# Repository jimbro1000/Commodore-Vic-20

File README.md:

# Commodore VIC-20 Schematic and PCB for assembly 250403

This repository contains KiCad schematics and "rough" PCB layout for the
cost reduced VIC-20, assembly #250403.

Originally hard forked from <https://github.com/StormTrooper/Commodore-Vic-20>
(this does not appear to be maintained).

The schematic for the Commodore VIC-20 (251027-01 Rev D) was taken from the
schematics on zimmers.net with extra detail from the "Vic-20 friendly computer
technical manual" and converted into KiCad (Version 8).

Additionally includes some KiCad footprints and symbols for the custom components.

## State

The schematics are complete and 95% of the PCB layout is done but it is not
complete. The power supply section of the board is mostly unfinished, and
accurate footprints for the large inductor, power switch and bridge rectifier are
needed.

## Notes

This is a WIP as the documentation and detail on the actual PCB are far from
clear and require some deciphering.

The power management section of the board in particular is unfinished.

The PCB design, while true to the original, is not intended for fabrication.
Instead the board has been reconstructed for the purpose of diagnosing faults
on original Commodore boards. The overall board dimensions are accurate but
the positioning of the different ports are approximations based on the rather
distorted board scans in the technical manual.

## KiCad thumbnail of schematic and pcb

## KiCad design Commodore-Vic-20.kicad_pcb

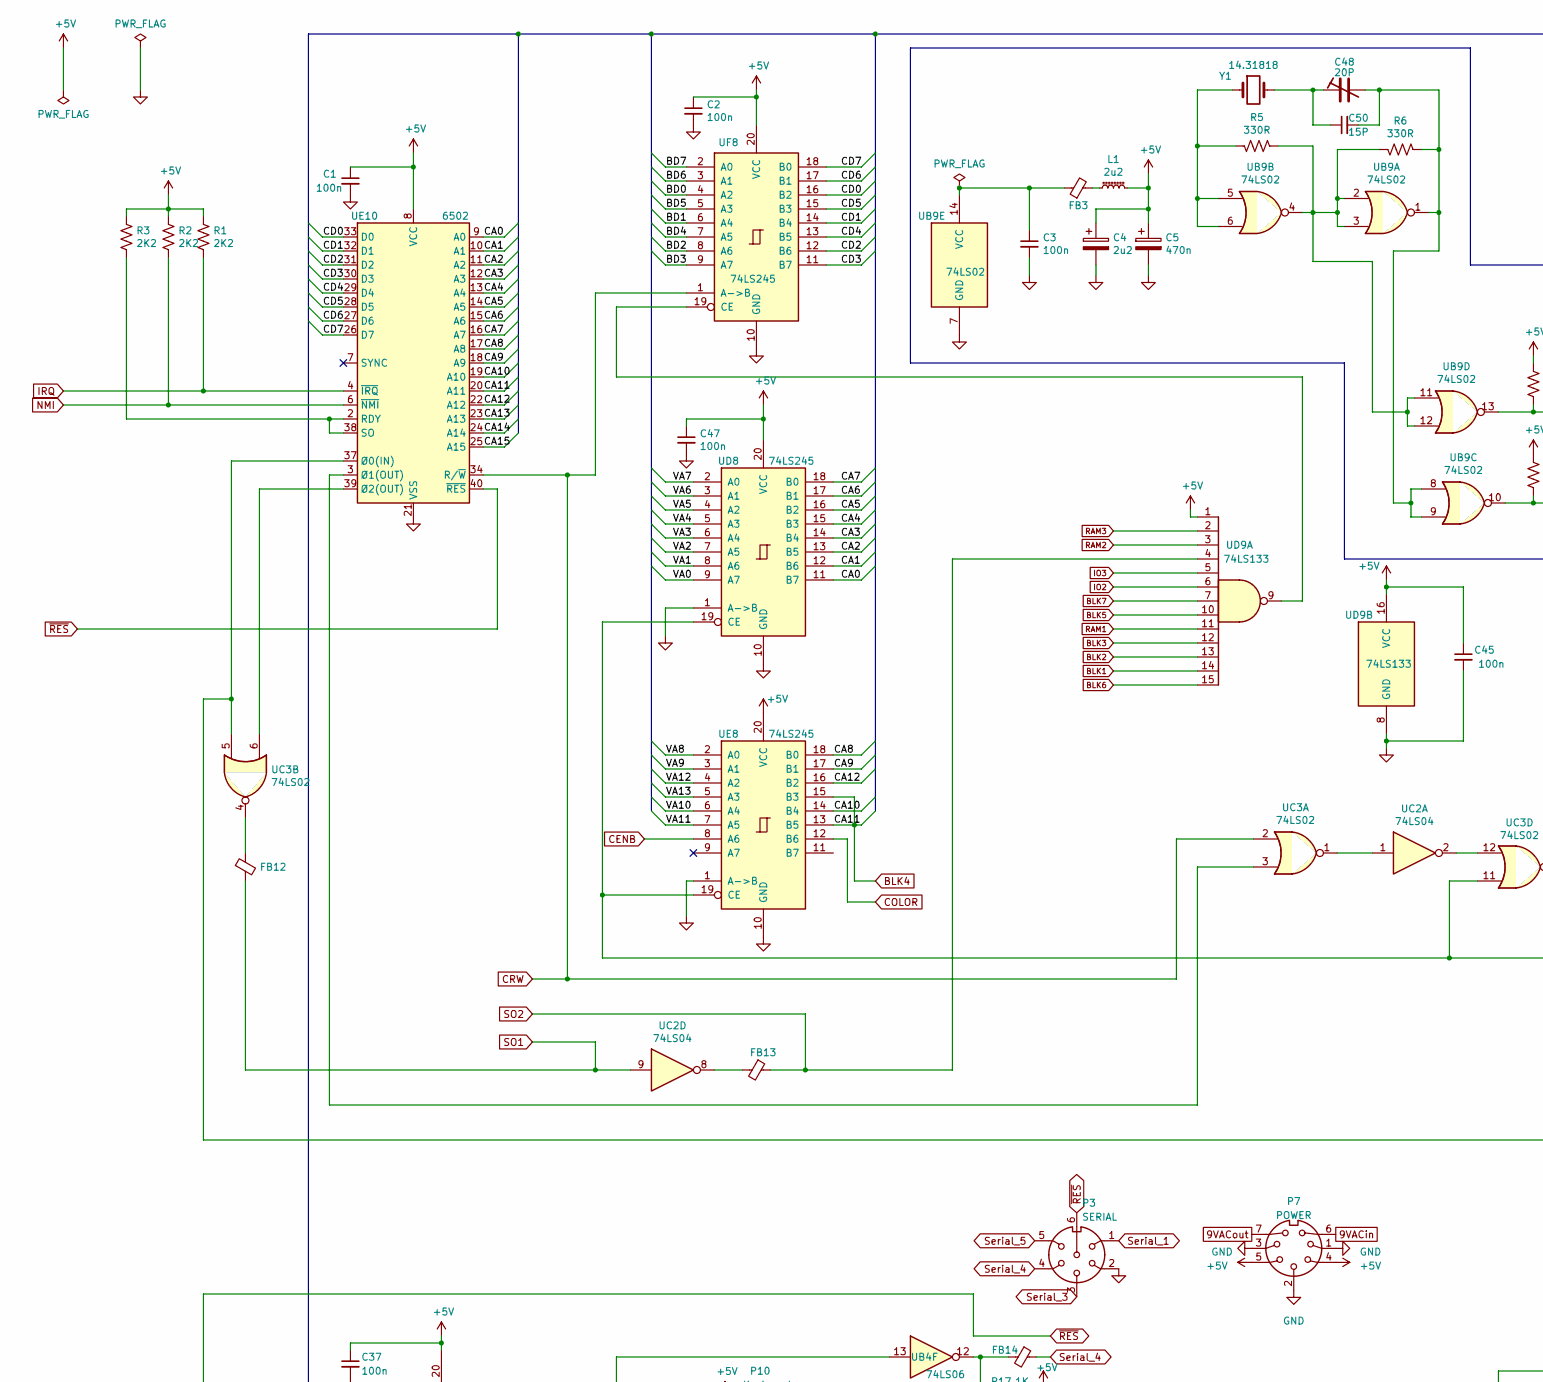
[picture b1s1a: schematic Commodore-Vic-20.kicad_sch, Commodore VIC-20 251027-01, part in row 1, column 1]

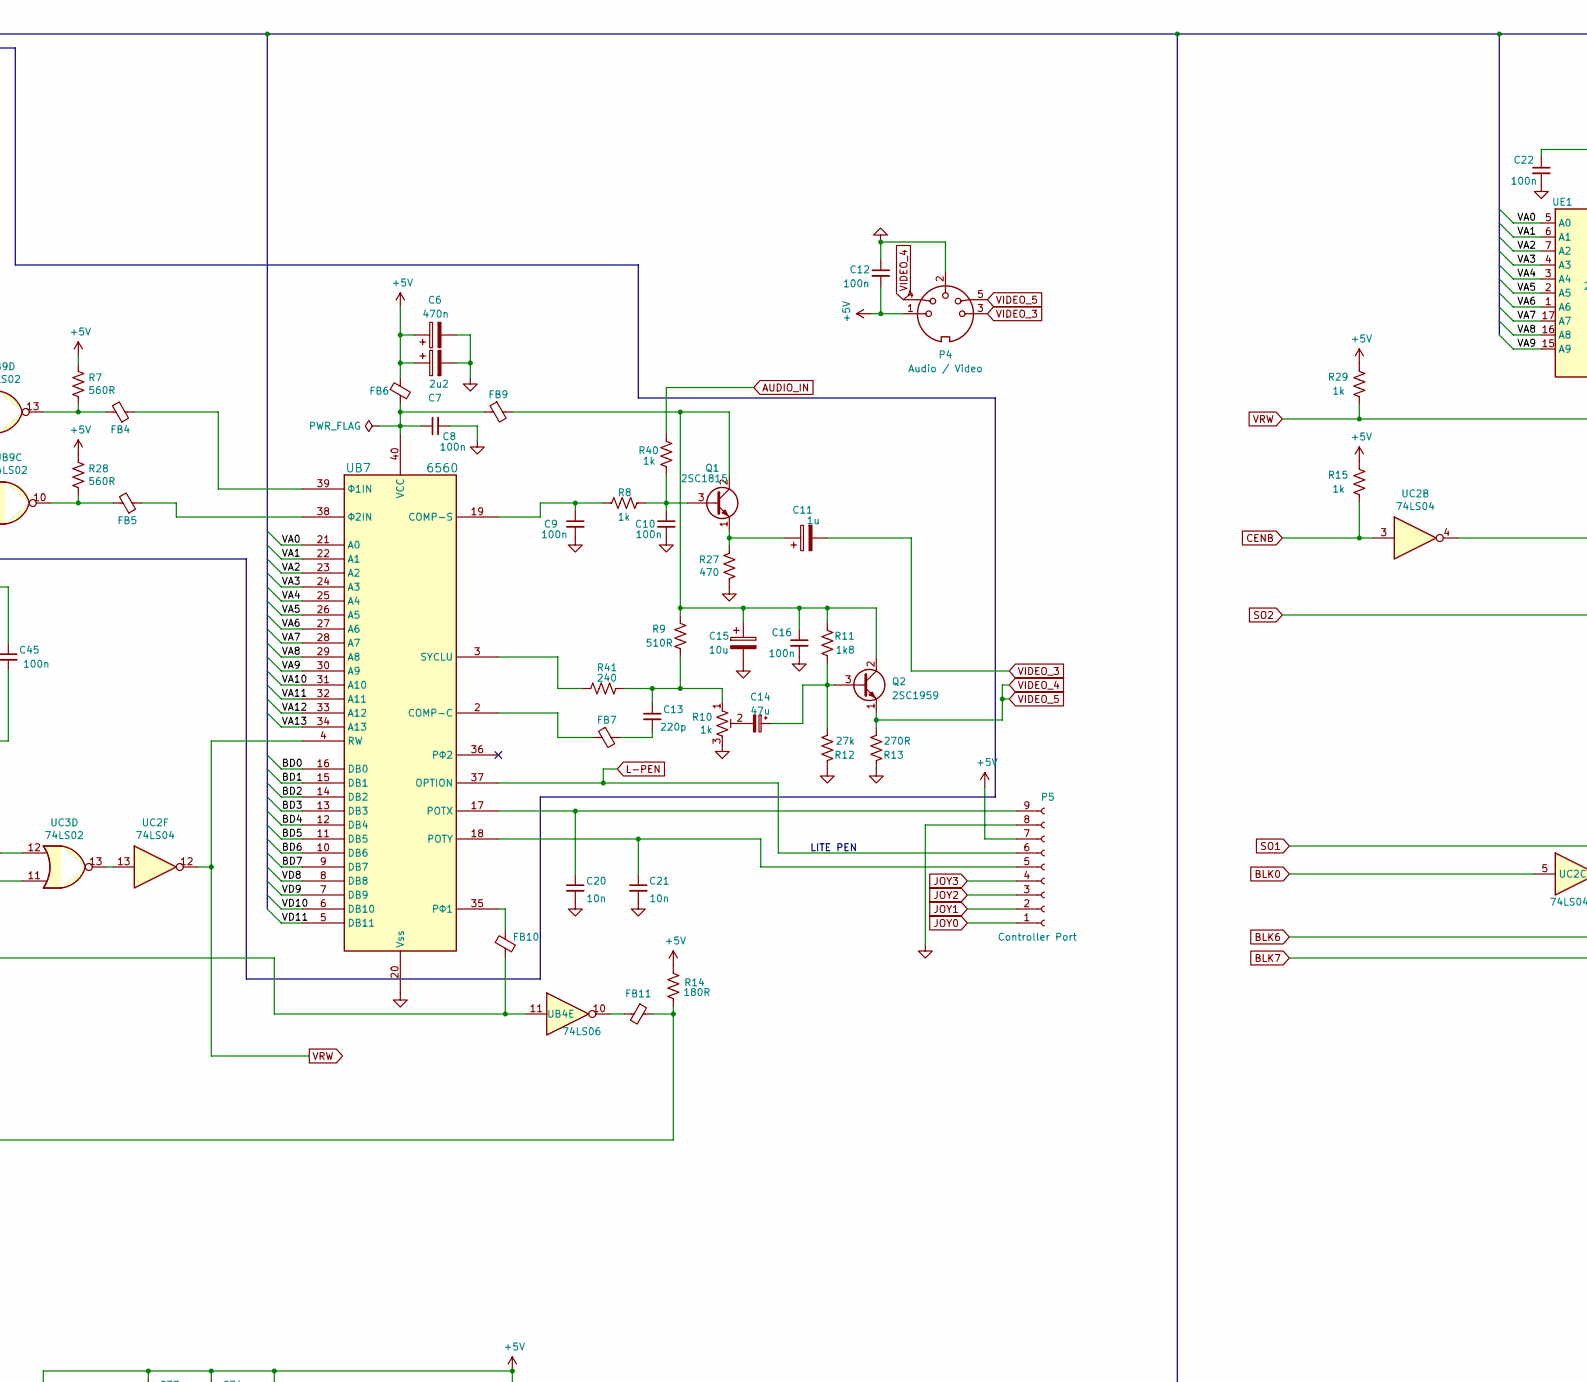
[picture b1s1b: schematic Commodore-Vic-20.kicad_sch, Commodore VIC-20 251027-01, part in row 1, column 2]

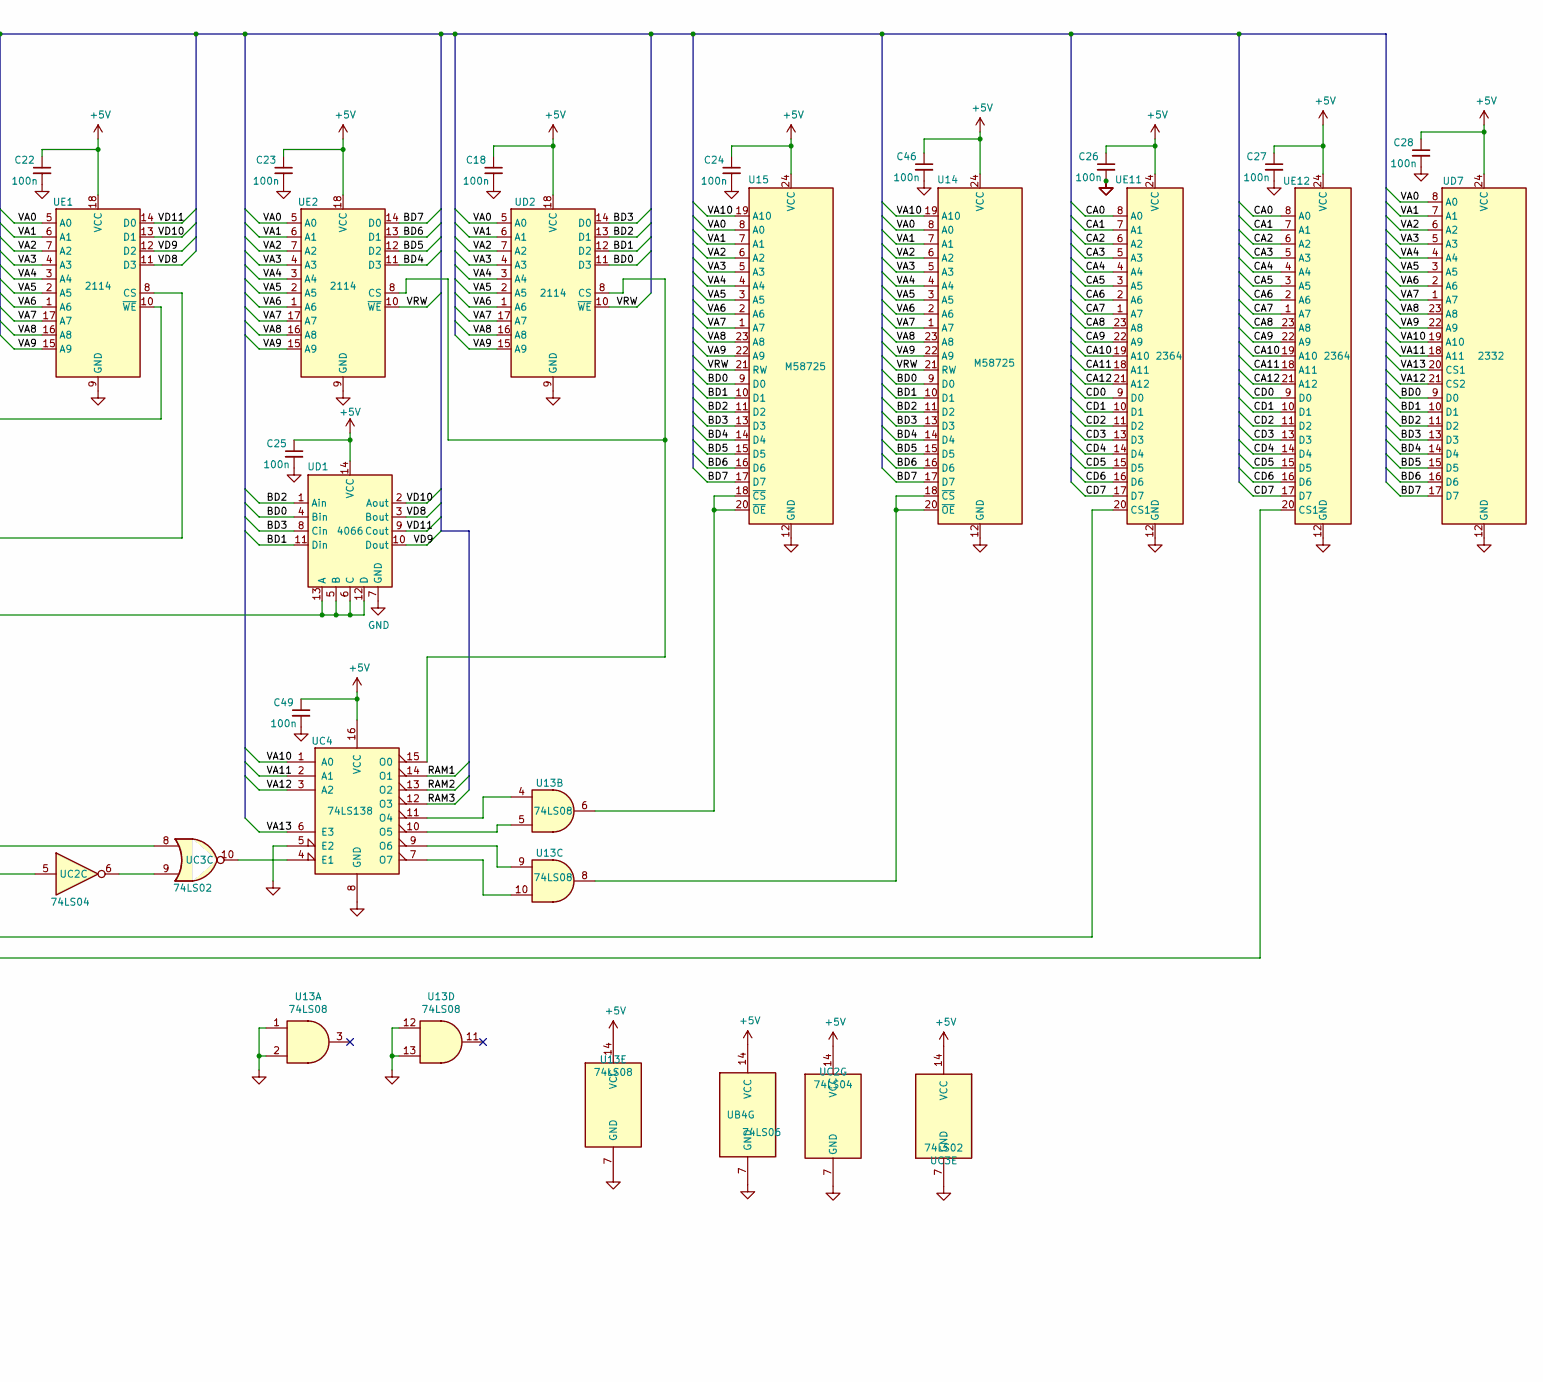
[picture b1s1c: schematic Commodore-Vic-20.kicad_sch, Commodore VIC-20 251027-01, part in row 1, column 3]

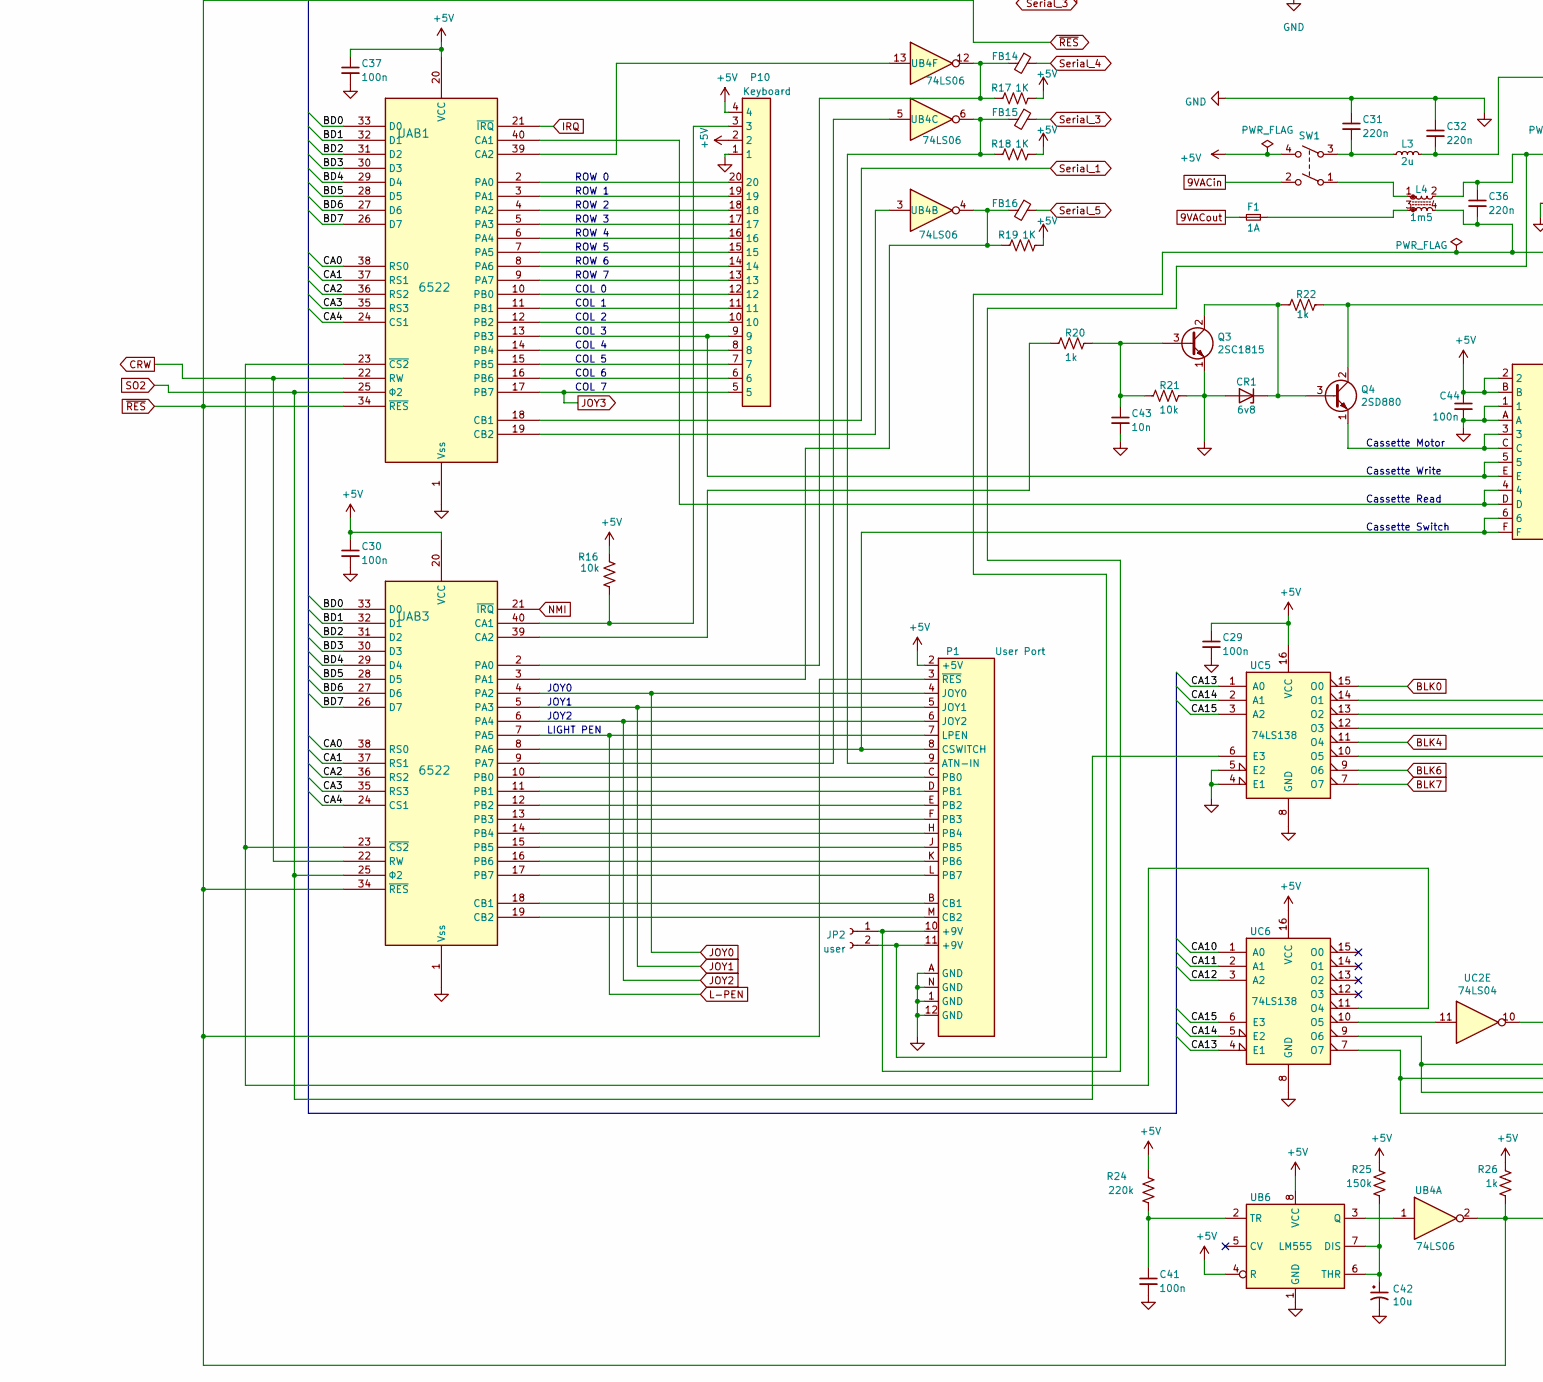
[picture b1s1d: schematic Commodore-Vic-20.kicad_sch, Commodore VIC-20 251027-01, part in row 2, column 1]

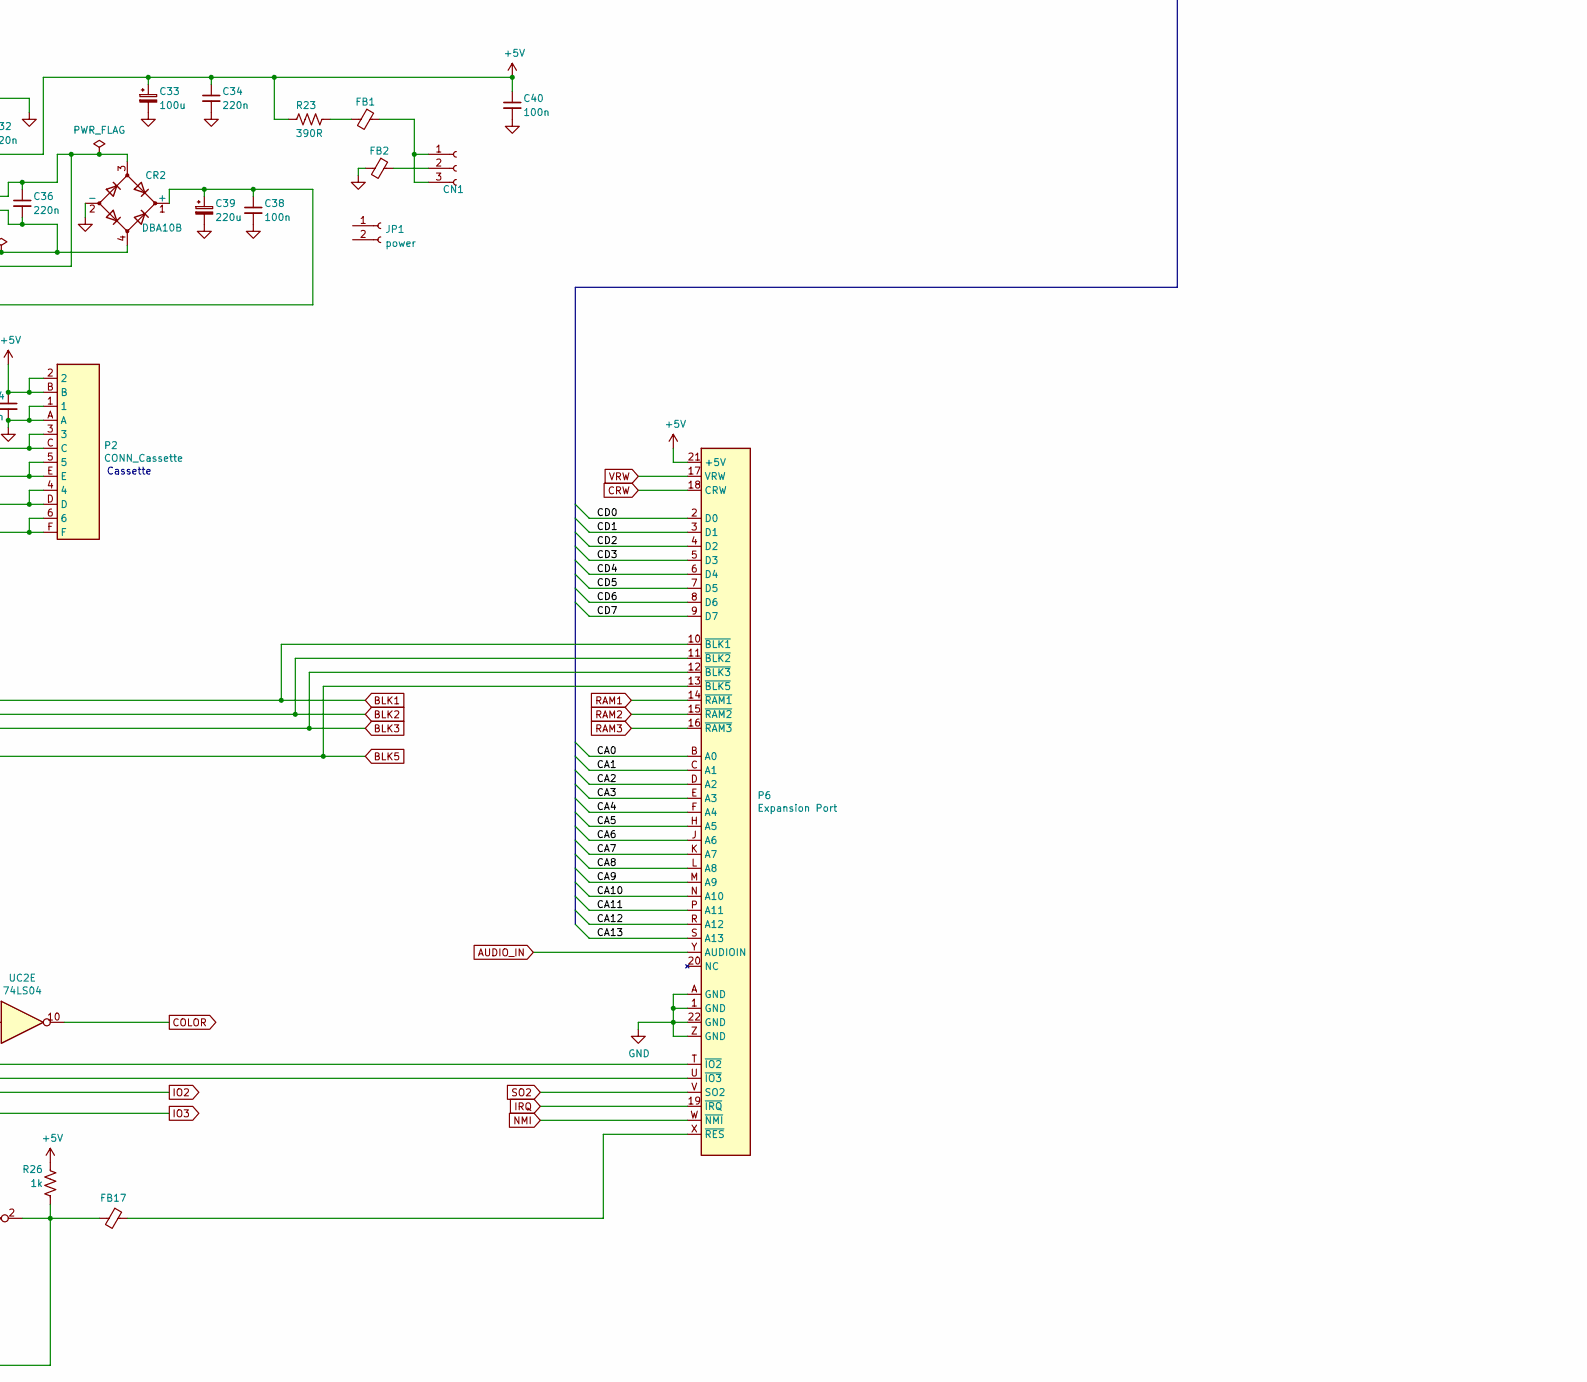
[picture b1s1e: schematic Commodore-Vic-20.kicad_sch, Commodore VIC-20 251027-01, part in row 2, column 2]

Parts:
C1, C2, C3, C8, C9, C10, C12, C16, C18, C22, C23, C24, C25, C26, C27, C28, C29, C30, C37, C38, C40, C41, C44, C45, C46, C47, C49: 100n; C_Disc_D4.7mm_W2.5mm_P5.00mm
C4, C7: 2u2; CP_Radial_D5.0mm_P2.50mm
C5: 470n; C_Disc_D4.7mm_W2.5mm_P5.00mm
C6: 470n; CP_Radial_D5.0mm_P2.50mm
C11: 1u; CP_Radial_D5.0mm_P5.0mm
C13: 220p; C_Disc_D4.7mm_W2.5mm_P5.00mm
C14: 47u; CP_Radial_D5.0mm_P5.0mm
C15, C42: 10u; CP_Radial_D5.0mm_P5.0mm
C20, C21, C43: 10n; C_Disc_D4.7mm_W2.5mm_P5.00mm
C31, C32, C34: 220n; C_Disc_D4.7mm_W2.5mm_P5.00mm
C33: 100u; CP_Radial_D8.0mm_P5.00mm
C36: 220n; C_Rect_L11.0mm_W2.8mm_P10.00mm_MKT
C39: 220u; CP_Axial_L38.0mm_D21.0mm_P44.00mm_Horizontal
C48: 20P; RV_Disc_D7mm_W3.4mm_P5mm
C50: 15P; C_Disc_D4.3mm_W1.9mm_P5.00mm
CN1: Conn_01x03_Female; PinHeader_1x03_P2.54mm_Vertical
CR1: 6v8; D_DO-34_SOD68_P10.16mm_Horizontal
CR2: DBA10B; Diode_Bridge_Vishay_KBPM
F1: 1A; Fuseholder_Cylinder-5x20mm_Stelvio-Kontek_PTF78_Horizontal_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
FB1, FB2, FB3, FB6, FB10, FB11, FB12, FB13, FB14, FB15, FB16, FB17: Ferrite_Bead_Small; L_Axial_L7.0mm_D3.3mm_P12.70mm_Horizontal_Fastron_MICC
FB4, FB5, FB7, FB9: Ferrite_Bead_Small; L_Axial_L7.0mm_D3.3mm_P5.08mm_Vertical_Fastron_MICC
JP1: power; PinSocket_1x02_P2.54mm_Vertical
JP2: user; PinSocket_1x02_P2.54mm_Vertical
L1: 2u2; L_Axial_L6.6mm_D2.7mm_P10.16mm_Horizontal_Vishay_IM-2
L3: 2u; L_Axial_L9.5mm_D4.0mm_P15.24mm_Horizontal_Fastron_SMCC
L4: 1m5; Diode_Bridge_15.2x15.2x6.3mm_P10.9mm
P1: User Port; VC20_USERPORT
P2: CONN_Cassette; VC20_CASSETTE
P3: SERIAL; DIN-6
P4: Audio / Video; DIN-5
P5: Controller Port; DSUB-9_Male_Horizontal_P2.77x2.54mm_EdgePinOffset9.40mm
P6: Expansion Port; VC20_EXPANSIONPORT
P7: POWER; DIN-7
P10: Keyboard; PinHeader_1x21_P2.54mm_Vertical
Q1, Q3: 2SC1815; TO-92_Inline_Wide
Q2: 2SC1959; TO-92_Inline_Wide
Q4: 2SD880; TO-220-3_Vertical
R1, R2, R3: 2K2; R_Axial_DIN0207_L6.3mm_D2.5mm_P10.16mm_Horizontal
R5, R6: 330R; R_Axial_DIN0207_L6.3mm_D2.5mm_P5.08mm_Vertical
R7, R28: 560R; R_Axial_DIN0207_L6.3mm_D2.5mm_P5.08mm_Vertical
R8, R40: 1k; R_Axial_DIN0207_L6.3mm_D2.5mm_P5.08mm_Vertical
R9: 510R; R_Axial_DIN0207_L6.3mm_D2.5mm_P5.08mm_Vertical
R10, R15, R20, R22, R26, R29: 1k; R_Axial_DIN0207_L6.3mm_D2.5mm_P10.16mm_Horizontal
R11: 1k8; R_Axial_DIN0207_L6.3mm_D2.5mm_P5.08mm_Vertical
R12: 27k; R_Axial_DIN0207_L6.3mm_D2.5mm_P5.08mm_Vertical
R13: 270R; R_Axial_DIN0207_L6.3mm_D2.5mm_P5.08mm_Vertical
R14: 180R; R_Axial_DIN0207_L6.3mm_D2.5mm_P10.16mm_Horizontal
R16, R21: 10k; R_Axial_DIN0207_L6.3mm_D2.5mm_P10.16mm_Horizontal
R17, R18, R19: 1K; R_Axial_DIN0207_L6.3mm_D2.5mm_P10.16mm_Horizontal
R23: 390R; R_Axial_DIN0207_L6.3mm_D2.5mm_P10.16mm_Horizontal
R24: 220k; R_Axial_DIN0207_L6.3mm_D2.5mm_P10.16mm_Horizontal
R25: 150k; R_Axial_DIN0207_L6.3mm_D2.5mm_P10.16mm_Horizontal
R27: 470; R_Axial_DIN0207_L6.3mm_D2.5mm_P5.08mm_Vertical
R41: 240; R_Axial_DIN0207_L6.3mm_D2.5mm_P5.08mm_Vertical
SW1: SW_DPST; SW_Push_2P1T_Toggle_CK_PVA1xxH1xxxxxxV2
U13: 74LS08; DIP-14_W7.62mm
U14, U15: M58725; DIP-24_W15.24mm
UAB1, UAB3: 6522; DIP-40_W15.24mm
UB4: 74LS06; DIP-14_W7.62mm
UB6: LM555; DIP-8_W7.62mm
UB7: 6560; DIP-40_W15.24mm
UB9: 74LS02; DIP-14_W7.62mm
UC2: 74LS04; DIP-14_W7.62mm
UC3: 74LS02; DIP-14_W7.62mm
UC4, UC5, UC6: 74LS138; DIP-16_W7.62mm
UD1: 4066; DIP-14_W7.62mm
UD2: 2114; DIP-18_W7.62mm
UD7: 2332; DIP-24_W15.24mm
UD8: 74LS245; DIP-20_W7.62mm
UD9: 74LS133; DIP-16_W7.62mm
UE1, UE2: 2114; DIP-18_W7.62mm
UE8: 74LS245; DIP-20_W7.62mm
UE10: 6502; DIP-40_W15.24mm
UE11, UE12: 2364; DIP-24_W15.24mm
UF8: 74LS245; DIP-20_W7.62mm
Y1: 14.31818; Crystal_HC18-U_Vertical

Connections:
9VACin: P7.6, SW1.2
9VACout: F1.2, P7.7
+5V: C1.1, C2.1, C4.1, C5.1, C6.1, C7.1, C12.2, C18.1, C22.1, C23.1, C24.1, C25.1, C26.1, C27.1, C28.1, C29.1, C30.1, C32.2, C33.1, C34.1, C37.1, C40.1, C44.1, C45.1, C46.1, C47.1, C49.1, FB6.1, L1.2, L3.2, P1.2 (+5V), P2.2, P2.B, P4.1, P5.7, P6.21 (+5V), P7.4, P7.5, P10.2, P10.4, R1.1, R2.1, R3.1, R7.2, R14.1, R15.1, R16.1, R17.1, R18.1, R19.1, R23.1, R24.1, R25.1, R26.1, R28.2, R29.1, SW1.4, U13.14 (VCC), U14.24 (VCC), U15.24 (VCC), UAB1.20 (VCC), UAB3.20 (VCC), UB4.14 (VCC), UB6.4 (R), UB6.8 (VCC), UC2.14 (VCC), UC3.14 (VCC), UC4.16 (VCC), UC5.16 (VCC), UC6.16 (VCC), UD1.14 (VCC), UD2.18 (VCC), UD7.24 (VCC), UD8.20 (VCC), UD9.1, UD9.16 (VCC), UE1.18 (VCC), UE2.18 (VCC), UE8.20 (VCC), UE10.8 (VCC), UE11.24 (VCC), UE12.24 (VCC), UF8.20 (VCC)
/BD0: U14.9 (D0), U15.9 (D0), UAB1.33 (D0), UAB3.33 (D0), UB7.16 (DB0), UD1.4 (Bin), UD2.11 (D3), UD7.9 (D0), UF8.4 (A2)
/BD1: U14.10 (D1), U15.10 (D1), UAB1.32 (D1), UAB3.32 (D1), UB7.15 (DB1), UD1.11 (Din), UD2.12 (D2), UD7.10 (D1), UF8.6 (A4)
/BD2: U14.11 (D2), U15.11 (D2), UAB1.31 (D2), UAB3.31 (D2), UB7.14 (DB2), UD1.1 (Ain), UD2.13 (D1), UD7.11 (D2), UF8.8 (A6)
/BD3: U14.13 (D3), U15.13 (D3), UAB1.30 (D3), UAB3.30 (D3), UB7.13 (DB3), UD1.8 (Cin), UD2.14 (D0), UD7.13 (D3), UF8.9 (A7)
/BD4: U14.14 (D4), U15.14 (D4), UAB1.29 (D4), UAB3.29 (D4), UB7.12 (DB4), UD7.14 (D4), UE2.11 (D3), UF8.7 (A5)
/BD5: U14.15 (D5), U15.15 (D5), UAB1.28 (D5), UAB3.28 (D5), UB7.11 (DB5), UD7.15 (D5), UE2.12 (D2), UF8.5 (A3)
/BD6: U14.16 (D6), U15.16 (D6), UAB1.27 (D6), UAB3.27 (D6), UB7.10 (DB6), UD7.16 (D6), UE2.13 (D1), UF8.3 (A1)
/BD7: U14.17 (D7), U15.17 (D7), UAB1.26 (D7), UAB3.26 (D7), UB7.9 (DB7), UD7.17 (D7), UE2.14 (D0), UF8.2 (A0)
/CA0: P6.B (A0), UAB1.38 (RS0), UAB3.38 (RS0), UD8.11 (B7), UE10.9 (A0), UE11.8 (A0), UE12.8 (A0)
/CA1: P6.C (A1), UAB1.37 (RS1), UAB3.37 (RS1), UD8.12 (B6), UE10.10 (A1), UE11.7 (A1), UE12.7 (A1)
/CA2: P6.D (A2), UAB1.36 (RS2), UAB3.36 (RS2), UD8.13 (B5), UE10.11 (A2), UE11.6 (A2), UE12.6 (A2)
/CA3: P6.E (A3), UAB1.35 (RS3), UAB3.35 (RS3), UD8.14 (B4), UE10.12 (A3), UE11.5 (A3), UE12.5 (A3)
/CA4: P6.F (A4), UAB1.24 (CS1), UAB3.24 (CS1), UD8.15 (B3), UE10.13 (A4), UE11.4 (A4), UE12.4 (A4)
/CA5: P6.H (A5), UD8.16 (B2), UE10.14 (A5), UE11.3 (A5), UE12.3 (A5)
/CA6: P6.J (A6), UD8.17 (B1), UE10.15 (A6), UE11.2 (A6), UE12.2 (A6)
/CA7: P6.K (A7), UD8.18 (B0), UE10.16 (A7), UE11.1 (A7), UE12.1 (A7)
/CA8: P6.L (A8), UE8.18 (B0), UE10.17 (A8), UE11.23 (A8), UE12.23 (A8)
/CA9: P6.M (A9), UE8.17 (B1), UE10.18 (A9), UE11.22 (A9), UE12.22 (A9)
/CA10: P6.N (A10), UC6.1 (A0), UE8.14 (B4), UE10.19 (A10), UE11.19 (A10), UE12.19 (A10)
/CA12: P6.R (A12), UC6.3 (A2), UE8.16 (B2), UE10.22 (A12), UE11.21 (A12), UE12.21 (A12)
/CA13: P6.S (A13), UC5.1 (A0), UC6.4 (E1), UE10.23 (A13)
/CA14: UC5.2 (A1), UC6.5 (E2), UE10.24 (A14)
/CA15: UC5.3 (A2), UC6.6 (E3), UE10.25 (A15)
/CD0: P6.2 (D0), UE10.33 (D0), UE11.9 (D0), UE12.9 (D0), UF8.16 (B2)
/CD1: P6.3 (D1), UE10.32 (D1), UE11.10 (D1), UE12.10 (D1), UF8.14 (B4)
/CD2: P6.4 (D2), UE10.31 (D2), UE11.11 (D2), UE12.11 (D2), UF8.12 (B6)
/CD3: P6.5 (D3), UE10.30 (D3), UE11.13 (D3), UE12.13 (D3), UF8.11 (B7)
/CD4: P6.6 (D4), UE10.29 (D4), UE11.14 (D4), UE12.14 (D4), UF8.13 (B5)
/CD5: P6.7 (D5), UE10.28 (D5), UE11.15 (D5), UE12.15 (D5), UF8.15 (B3)
/CD6: P6.8 (D6), UE10.27 (D6), UE11.16 (D6), UE12.16 (D6), UF8.17 (B1)
/CD7: P6.9 (D7), UE10.26 (D7), UE11.17 (D7), UE12.17 (D7), UF8.18 (B0)
/VA0: U14.8 (A0), U15.8 (A0), UB7.21 (A0), UD2.5 (A0), UD7.8 (A0), UD8.9 (A7), UE1.5 (A0), UE2.5 (A0)
/VA1: U14.7 (A1), U15.7 (A1), UB7.22 (A1), UD2.6 (A1), UD7.7 (A1), UD8.8 (A6), UE1.6 (A1), UE2.6 (A1)
/VA2: U14.6 (A2), U15.6 (A2), UB7.23 (A2), UD2.7 (A2), UD7.6 (A2), UD8.7 (A5), UE1.7 (A2), UE2.7 (A2)
/VA3: U14.5 (A3), U15.5 (A3), UB7.24 (A3), UD2.4 (A3), UD7.5 (A3), UD8.6 (A4), UE1.4 (A3), UE2.4 (A3)
/VA4: U14.4 (A4), U15.4 (A4), UB7.25 (A4), UD2.3 (A4), UD7.4 (A4), UD8.5 (A3), UE1.3 (A4), UE2.3 (A4)
/VA5: U14.3 (A5), U15.3 (A5), UB7.26 (A5), UD2.2 (A5), UD7.3 (A5), UD8.4 (A2), UE1.2 (A5), UE2.2 (A5)
/VA6: U14.2 (A6), U15.2 (A6), UB7.27 (A6), UD2.1 (A6), UD7.2 (A6), UD8.3 (A1), UE1.1 (A6), UE2.1 (A6)
/VA7: U14.1 (A7), U15.1 (A7), UB7.28 (A7), UD2.17 (A7), UD7.1 (A7), UD8.2 (A0), UE1.17 (A7), UE2.17 (A7)
/VA8: U14.23 (A8), U15.23 (A8), UB7.29 (A8), UD2.16 (A8), UD7.23 (A8), UE1.16 (A8), UE2.16 (A8), UE8.2 (A0)
/VA9: U14.22 (A9), U15.22 (A9), UB7.30 (A9), UD2.15 (A9), UD7.22 (A9), UE1.15 (A9), UE2.15 (A9), UE8.3 (A1)
/VA10: U14.19 (A10), U15.19 (A10), UB7.31 (A10), UC4.1 (A0), UD7.19 (A10), UE8.6 (A4)
/VA11: UB7.32 (A11), UC4.2 (A1), UD7.18 (A11), UE8.7 (A5)
/VA12: UB7.33 (A12), UC4.3 (A2), UD7.21 (CS2), UE8.4 (A2)
/VA13: UB7.34 (A13), UC4.6 (E3), UD7.20 (CS1), UE8.5 (A3)
/VD8: UB7.8 (DB8), UD1.3 (Bout), UE1.11 (D3)
/VD9: UB7.7 (DB9), UD1.10 (Dout), UE1.12 (D2)
/VD10: UB7.6 (DB10), UD1.2 (Aout), UE1.13 (D1)
/VD11: UB7.5 (DB11), UD1.9 (Cout), UE1.14 (D0)
AUDIO_IN: P6.Y (AUDIOIN), R40.1
BLK0: UC2.5, UC5.15 (O0)
BLK1: P6.10 (~BLK1), UC5.14 (O1), UD9.14
BLK2: P6.11 (~BLK2), UC5.13 (O2), UD9.13
BLK3: P6.12 (~BLK3), UC5.12 (O3), UD9.12
BLK4: P6.P (A11), UC5.11 (O4), UC6.2 (A1), UE8.13 (B5), UE8.15 (B3), UE10.20 (A11), UE11.18 (A11), UE12.18 (A11)
BLK5: P6.13 (~BLK5), UC5.10 (O5), UD9.10
BLK6: UC5.9 (O6), UD9.15, UE11.20 (CS1)
BLK7: UC5.7 (O7), UD9.7, UE12.20 (CS1)
CENB: R15.2, UC2.3, UE8.8 (A6)
COLOR: UC2.10, UE8.12 (B6)
CRW: P6.18 (CRW), UAB1.22 (RW), UAB3.22 (RW), UC3.2, UE10.34 (R/~W), UF8.1 (A->B)
GND: C1.2, C2.2, C3.2, C4.2, C5.2, C6.2, C7.2, C8.2, C9.2, C10.2, C12.1, C15.2, C16.2, C18.2, C20.2, C21.2, C22.2, C23.2, C24.2, C25.2, C26.2, C27.2, C28.2, C29.2, C30.2, C31.1, C32.1, C33.2, C34.2, C37.2, C38.2, C39.2, C40.2, C41.2, C42.2, C43.2, C44.2, C45.2, C46.2, C47.2, C49.2, CR1.2 (A), CR2.2 (-), FB2.2, P1.1 (GND), P1.12 (GND), P1.A (GND), P1.N (GND), P2.1, P2.A, P3.2, P4.2, P5.8, P6.1 (GND), P6.22 (GND), P6.A (GND), P6.Z (GND), P7.1, P7.2, P7.3, P10.1, Q3.1 (E), R10.3, R12.1, R13.1, R21.2, R27.1, U13.1, U13.2, U13.7 (GND), U13.12, U13.13, U14.12 (GND), U15.12 (GND), UAB1.1 (Vss), UAB3.1 (Vss), UB4.7 (GND), UB6.1 (GND), UB7.20 (Vss), UB9.7 (GND), UC2.7 (GND), UC3.7 (GND), UC4.5 (E2), UC4.8 (GND), UC5.4 (E1), UC5.5 (E2), UC5.8 (GND), UC6.8 (GND), UD1.7 (GND), UD2.9 (GND), UD7.12 (GND), UD8.1 (A->B), UD8.10 (GND), UD9.8 (GND), UE1.9 (GND), UE2.9 (GND), UE8.1 (A->B), UE8.10 (GND), UE10.1 (VSS), UE10.21 (VSS), UE11.12 (GND), UE12.12 (GND), UF8.10 (GND)
IO2: P6.T (~IO2), UC6.9 (O6), UD9.6
IO3: P6.U (~IO3), UC6.7 (O7), UD9.5
IRQ: P6.19 (~IRQ), R1.2, UAB1.21 (~IRQ), UE10.4 (~IRQ)
JOY0: P1.4 (JOY0), P5.1, UAB3.4 (PA2)
JOY1: P1.5 (JOY1), P5.2, UAB3.5 (PA3)
JOY2: P1.6 (JOY2), P5.3, UAB3.6 (PA4)
JOY3: P5.4, P10.5, UAB1.17 (PB7)
L-PEN: P1.7 (LPEN), P5.6, UAB3.7 (PA5), UB7.37 (OPTION)
NMI: P6.W (~NMI), R2.2, UAB3.21 (~IRQ), UE10.6 (~NMI)
unnamed: C8.1, FB6.2, FB9.1, UB7.40 (VCC)
unnamed: C36.1, CR2.3, JP2.1, L4.2, P1.10 (+9V)
unnamed: C36.2, CR2.4, JP2.2, L4.4, P1.11 (+9V)
unnamed: C3.1, FB3.1, UB9.14 (VCC)
unnamed: C13.1, R9.2, R10.1, R41.2
unnamed: C13.2, FB7.2
unnamed: C14.2, R10.2
unnamed: C31.2, L3.1, SW1.3
unnamed: C48.1, C50.1, Y1.2
unnamed: C48.2, C50.2, R6.2, UB9.1, UB9.8, UB9.9
unnamed: CN1.1, CN1.3, FB1.1
unnamed: CN1.2, FB2.1
unnamed: CR1.1 (K), Q3.2 (C), Q4.3 (B), R22.1
unnamed: C38.1, C39.1, CR2.1 (+), Q4.2 (C), R22.2
unnamed: F1.1, L4.3
unnamed: FB1.2, R23.2
unnamed: FB3.2, L1.1
unnamed: FB4.2, R7.1, UB9.13
unnamed: FB5.2, R28.1, UB9.10
unnamed: FB11.2, UB4.10
unnamed: FB12.1, UC3.4
unnamed: FB13.2, UC2.8
unnamed: L4.1, SW1.1
unnamed: FB15.2, P1.9 (ATN-IN), R18.2, UB4.6
unnamed: P1.B (CB1), UAB3.18 (CB1)
unnamed: P1.M (CB2), UAB3.19 (CB2)
unnamed: P1.8 (CSWITCH), P2.6, P2.F, UAB3.8 (PA6)
unnamed: P1.C (PB0), UAB3.10 (PB0)
unnamed: P1.D (PB1), UAB3.11 (PB1)
unnamed: P1.E (PB2), UAB3.12 (PB2)
unnamed: P1.F (PB3), UAB3.13 (PB3)
unnamed: P1.H (PB4), UAB3.14 (PB4)
unnamed: P1.J (PB5), UAB3.15 (PB5)
unnamed: P1.K (PB6), UAB3.16 (PB6)
unnamed: P1.L (PB7), UAB3.17 (PB7)
unnamed: C21.1, P5.5, UB7.18 (POTY)
unnamed: C20.1, P5.9, UB7.17 (POTX)
unnamed: FB17.1, P6.X (~RES)
unnamed: C10.1, Q1.3 (B), R8.2, R40.2
unnamed: C15.1, C16.1, FB9.2, Q1.2 (C), Q2.2 (C), R9.1, R11.1
unnamed: C11.1, Q1.1 (E), R27.2
unnamed: C14.1, Q2.3 (B), R11.2, R12.2
unnamed: C43.1, Q3.3 (B), R20.2, R21.1
unnamed: P2.3, P2.C, Q4.1 (E)
unnamed: R5.1, UB9.5, UB9.6, Y1.1
unnamed: R5.2, R6.1, UB9.2, UB9.3, UB9.4, UB9.11, UB9.12
unnamed: U13.8, U14.18 (~CS), U14.20 (~OE)
unnamed: U13.6, U15.18 (~CS), U15.20 (~OE)
unnamed: P2.4, P2.D, UAB1.40 (CA1)
unnamed: UAB1.39 (CA2), UB4.13
unnamed: UAB1.19 (CB2), UB4.3
unnamed: P10.20, UAB1.2 (PA0)
unnamed: P10.19, UAB1.3 (PA1)
unnamed: P10.18, UAB1.4 (PA2)
unnamed: P10.17, UAB1.5 (PA3)
unnamed: P10.16, UAB1.6 (PA4)
unnamed: P10.15, UAB1.7 (PA5)
unnamed: P10.14, UAB1.8 (PA6)
unnamed: P10.13, UAB1.9 (PA7)
unnamed: P10.12, UAB1.10 (PB0)
unnamed: P10.11, UAB1.11 (PB1)
unnamed: P10.10, UAB1.12 (PB2)
unnamed: P2.5, P2.E, P10.9, UAB1.13 (PB3)
unnamed: P10.8, UAB1.14 (PB4)
unnamed: P10.7, UAB1.15 (PB5)
unnamed: P10.6, UAB1.16 (PB6)
unnamed: UAB1.23 (~CS2), UAB3.23 (~CS2), UC6.11 (O4)
unnamed: P10.3, R16.2, UAB3.40 (CA1)
unnamed: R20.1, UAB3.39 (CA2)
unnamed: FB14.2, R17.2, UAB3.2 (PA0), UB4.12
unnamed: FB16.2, R19.2, UAB3.3 (PA1), UB4.4
unnamed: UAB3.9 (PA7), UB4.5
unnamed: C42.1, R25.2, UB6.6 (THR), UB6.7 (DIS)
unnamed: UB4.1, UB6.3 (Q)
unnamed: C41.1, R24.2, UB6.2 (TR)
unnamed: FB7.1, UB7.2 (COMP-C)
unnamed: C9.1, R8.1, UB7.19 (COMP-S)
unnamed: FB10.1, UB7.35 (PФ1)
unnamed: R41.1, UB7.3 (SYCLU)
unnamed: FB4.1, UB7.39 (Ф1IN)
unnamed: FB5.1, UB7.38 (Ф2IN)
unnamed: UC2.1, UC3.1
unnamed: UC2.2, UC3.12
unnamed: UC2.6, UC3.9
unnamed: UC2.13, UC3.13
unnamed: UC3.10, UC4.4 (E1)
unnamed: UC4.15 (O0), UD2.8 (CS), UE2.8 (CS)
unnamed: U13.4, UC4.11 (O4)
unnamed: U13.5, UC4.10 (O5)
unnamed: U13.9, UC4.9 (O6)
unnamed: U13.10, UC4.7 (O7)
unnamed: UC2.11, UC6.10 (O5)
unnamed: FB10.2, UB4.11, UC3.11, UD8.19 (CE), UE8.19 (CE)
unnamed: UC2.4, UE1.8 (CS)
unnamed: R3.2, UE10.2 (RDY), UE10.38 (SO)
unnamed: FB11.1, R14.2, UC3.5, UE10.37 (Ø0(IN))
unnamed: UC3.3, UE10.3 (Ø1(OUT))
unnamed: UC3.6, UE10.39 (Ø2(OUT))
unnamed: UD9.9, UF8.19 (CE)
RAM1: P6.14 (~RAM1), UC4.14 (O1), UD9.11
RAM2: P6.15 (~RAM2), UC4.13 (O2), UD9.3
RAM3: P6.16 (~RAM3), UC4.12 (O3), UD9.2
SO1: FB12.2, UC2.9, UC3.8
SO2: FB13.1, P6.V (SO2), UAB1.25 (Φ2), UAB3.25 (Φ2), UC5.6 (E3), UD1.5 (B), UD1.6 (C), UD1.12 (D), UD1.13 (A), UD9.4
Serial_1: P3.1, UAB1.18 (CB1)
Serial_3: FB15.1, P3.3
Serial_4: FB14.1, P3.4
Serial_5: FB16.1, P3.5
VIDEO_3: C11.2, P4.3
VIDEO_4: P4.4, P4.5, Q2.1 (E), R13.2
VRW: P6.17 (VRW), R29.2, U14.21 (RW), U15.21 (RW), UB7.4 (RW), UC2.12, UD2.10 (~WE), UE1.10 (~WE), UE2.10 (~WE)
~RES: FB17.2, P1.3 (~RES), P3.6, R26.2, UAB1.34 (~RES), UAB3.34 (~RES), UB4.2, UE10.40 (~RES)

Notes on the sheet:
ROW 1
ROW 3
JOY0
Cassette Read
Cassette Motor
COL 0
COL 2
ROW 0
JOY2
Cassette Write
ROW 7
JOY1
ROW 5
ROW 6
LITE PEN
LIGHT PEN
COL 4
Cassette
ROW 2
COL 6
COL 3
COL 7
COL 5
Cassette Switch
COL 1
ROW 4

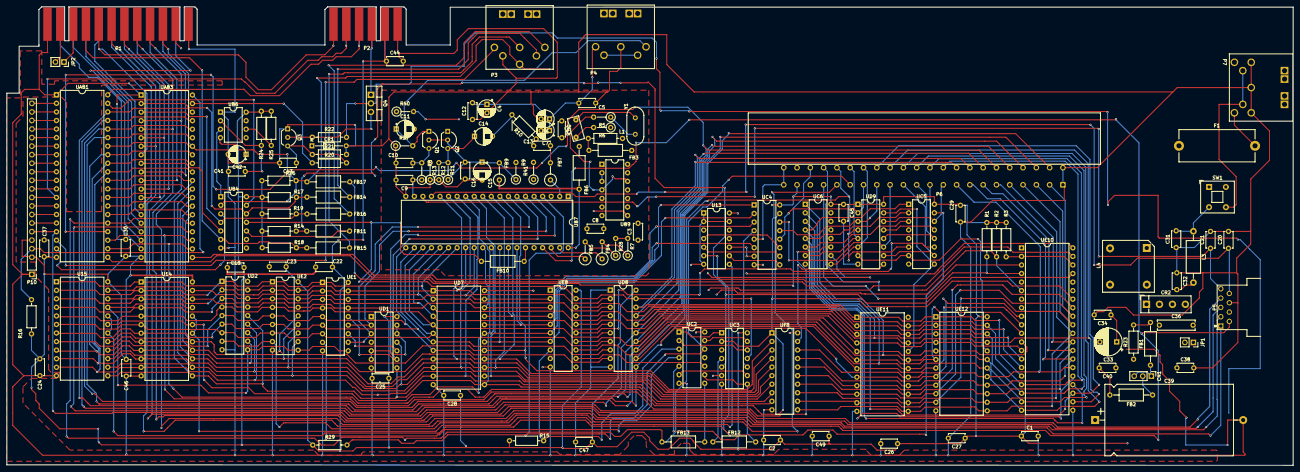
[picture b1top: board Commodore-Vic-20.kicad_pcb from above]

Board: 2 copper layers, 382.1 x 136.2 mm, 142 parts (0 on the bottom side), 186 nets.

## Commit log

2023-03-15 initial board design
2023-03-16 replicate original board
2023-03-16 fix inductor
2023-03-16 dimension inductor
2023-03-17 develop rear of board
2023-03-18 more wiring
2023-03-19 refresh project details
2023-03-19 add pdb render
2023-03-26 improve trace names
2023-04-02 progress traces
2024-08-10 resolve power circuit
2024-08-10 improve pcb
2024-08-10 colour code buses in schematics
